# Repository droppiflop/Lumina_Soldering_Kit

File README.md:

🇬🇧 English | 🇩🇪 [Deutsch](README.de.md)

# Lumina RC Fader

The solder kit **"Lumina RC Fader"** is the beginning of a learning platform that combines teaching electrical engineering with storytelling elements.

Lumina RC Fader is the second of three solder kits that build on one another. The boards tell the story of Lumina, a sorcery student who learns to bring magical crystals to life. Lumina's learning process, which takes her through trial and error to mastery of magic, mirrors the learning of students who gain their first experience in electrical engineering with a soldering iron and solder.

## Status

The solder kit is in its alpha phase.

## License

© 2026 Alexander Schmitz

This work is licensed under a [Creative Commons Attribution-NonCommercial-ShareAlike 4.0 International License (CC BY-NC-SA 4.0)](https://creativecommons.org/licenses/by-nc-sa/4.0/).

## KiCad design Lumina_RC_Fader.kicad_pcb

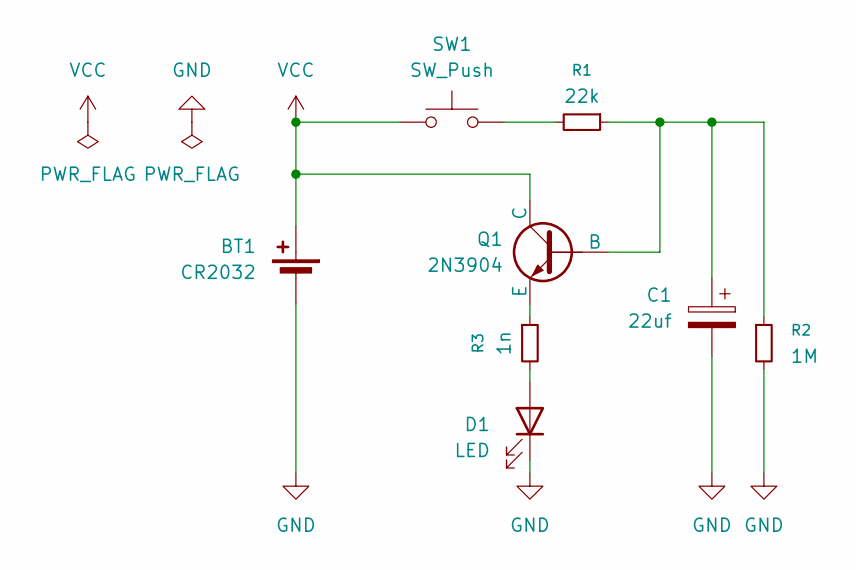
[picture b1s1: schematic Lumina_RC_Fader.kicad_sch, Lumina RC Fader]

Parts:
BT1: CR2032; custom_BatteryHolder_Keystone_1060_1x2032_MouserPN_712-BAT-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
C1: 22uf; custom_narrow_THtoSMD_CP_Axial_L11.0mm_D6.0mm_P18.00mm_Hori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
D1: LED; custom_narrow_LED_D5.0mm_Horizontal_O6.35mm_Z3.0mm_copy_cop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
Q1: 2N3904; custom_narrow_THtoSMD_TO-92_Inline_W4.0mm_Horizontal_FlatSi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
R1: 22k; custom_R_Axial_DIN0207_L6.3mm_D2.5mm_P10.16mm_Horizontal_Di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
R2: 1M; custom_R_Axial_DIN0207_L6.3mm_D2.5mm_P10.16mm_Horizontal_Di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
R3: 1n; custom_R_Axial_DIN0207_L6.3mm_D2.5mm_P10.16mm_Horizontal_Di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
SW1: SW_Push; custom_PadL_SWITCH_TACTILE_SPST_6x6_DigikeyPN_450-1650-ND_1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

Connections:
GND: BT1.2 (-), C1.2, D1.1 (K), R2.2
unnamed: D1.2 (A), R3.2
unnamed: C1.1, Q1.2 (B), R1.1, R2.1
unnamed: Q1.3 (E), R3.1
unnamed: R1.2, SW1.2
VCC: BT1.1 (+), Q1.1 (C), SW1.1

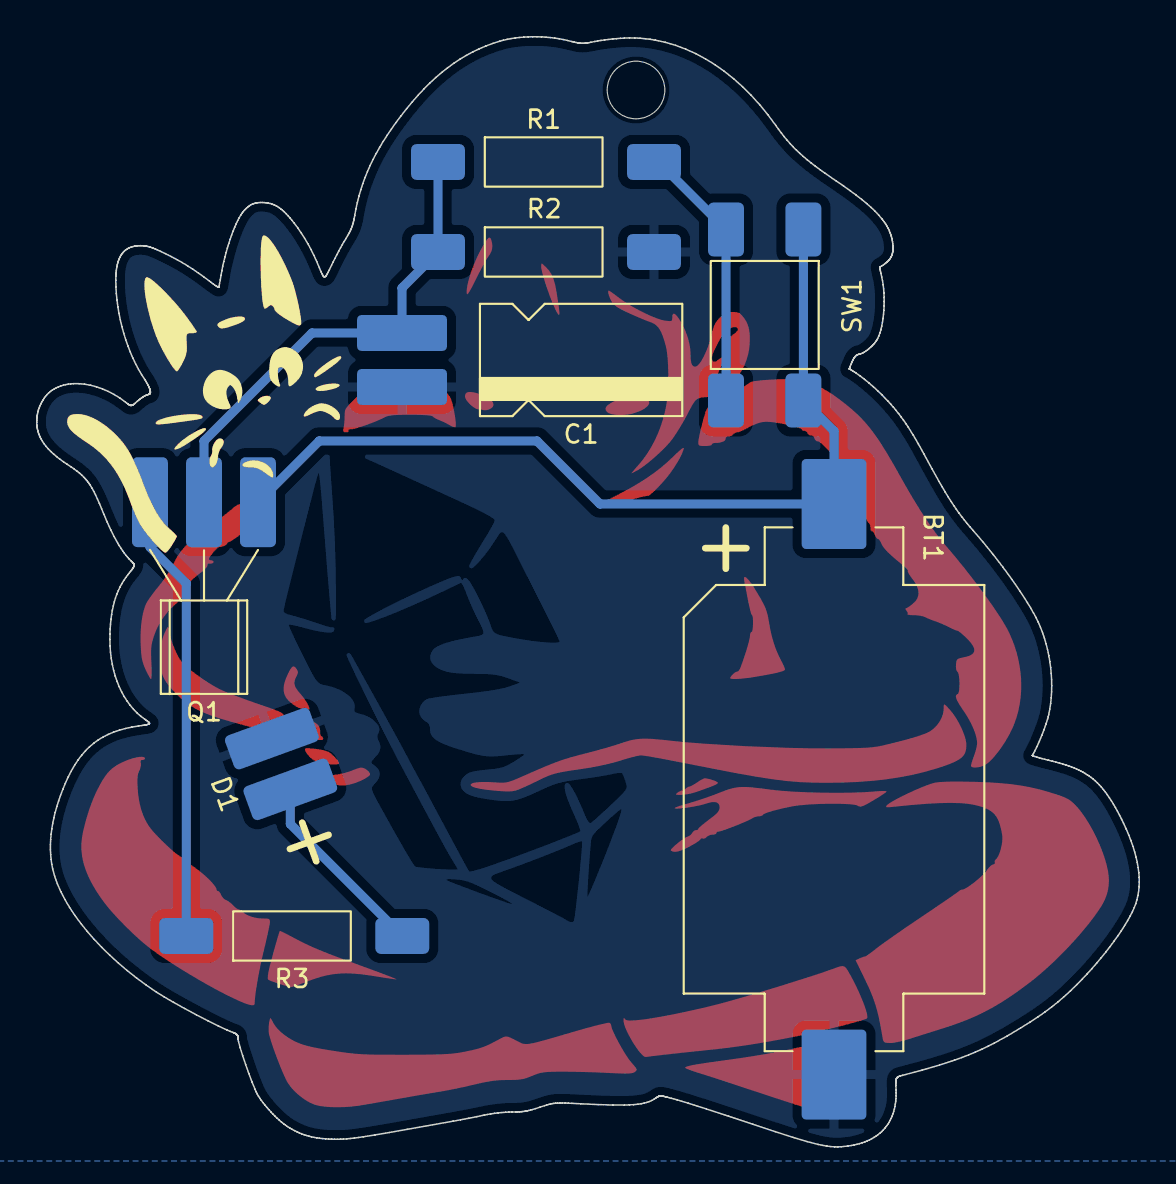
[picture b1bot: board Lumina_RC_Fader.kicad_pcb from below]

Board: 2 copper layers, 61.2 x 61.7 mm, 8 parts (8 on the bottom side), 6 nets.
